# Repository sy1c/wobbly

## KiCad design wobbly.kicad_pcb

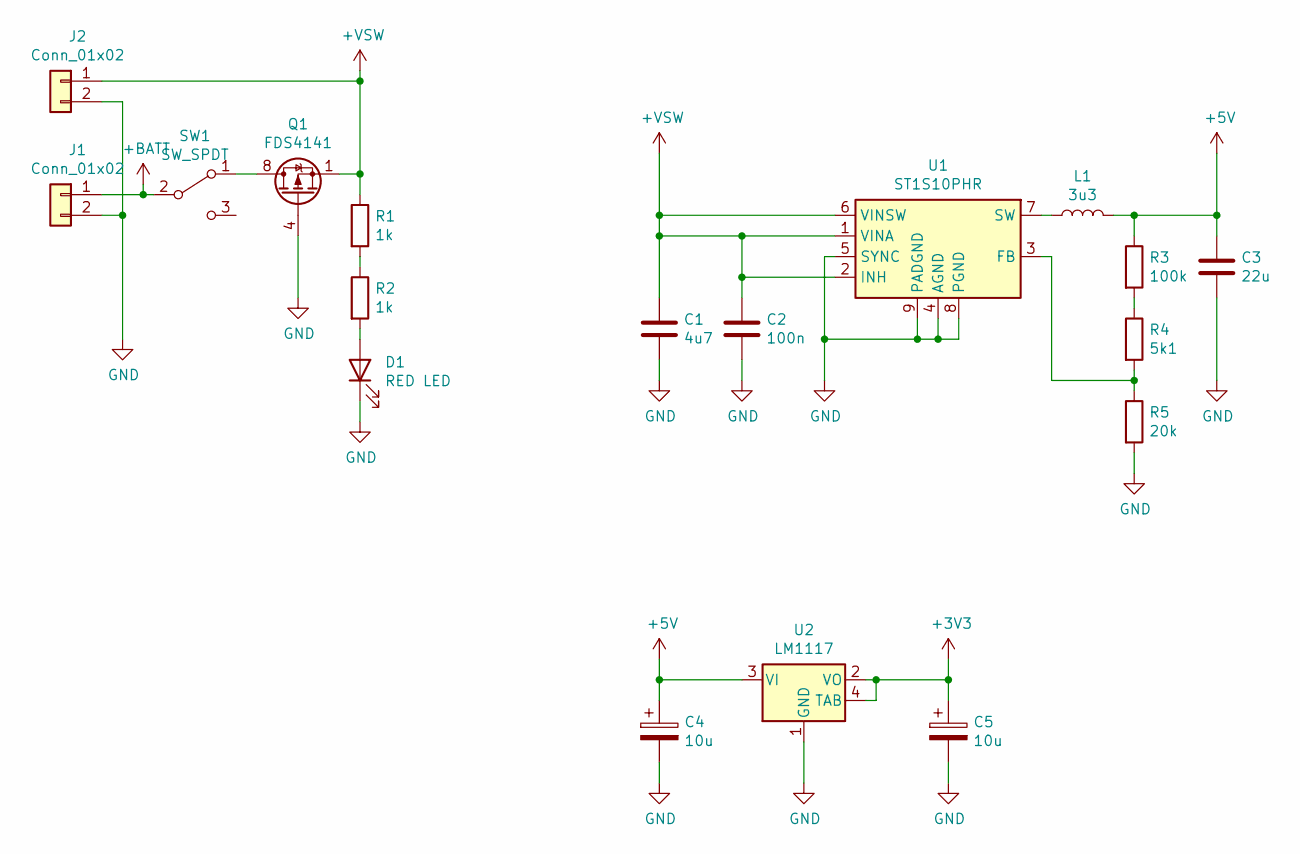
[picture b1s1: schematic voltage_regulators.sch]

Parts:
C1: 4u7; C_1206
C2: 100n; C_1206
C3: 22u; C_1210_Pad1.40x2.80mm
C4, C5: 10u; CP_2312
D1: RED LED; LED_0805
J1, J2: Conn_01x02; Degson_15EDGRC-3.5
L1: 3u3; L_TDK_RLF7030
Q1: FDS4141; SO-8
R1, R2: 1k; R_1206
R3: 100k; R_1206
R4: 5k1; R_1206
R5: 20k; R_1206
SW1: SW_SPDT; SW_Slide_CE_SL19121
U1: ST1S10PHR; Power_SO-8
U2: LM1117; SOT-223-4

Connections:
+3V3: C5.1, U2.2 (VO), U2.4 (TAB); also elsewhere on the board
+5V: C3.1, C4.1, L1.2, R3.1, U2.3 (VI); also elsewhere on the board
+BATT: J1.1, SW1.2 (B)
GND: C1.2, C2.2, C3.2, C4.2, C5.2, D1.1 (K), J1.2, J2.2, Q1.4 (G), R5.2, U1.4 (AGND), U1.5 (SYNC), U1.8 (PGND), U1.9 (PADGND), U2.1 (GND); also elsewhere on the board
unnamed: D1.2 (A), R2.2
unnamed: L1.1, U1.7 (SW)
unnamed: Q1.5 (D), Q1.6 (D), Q1.7 (D), Q1.8 (D), SW1.1 (A)
unnamed: R1.2, R2.1
unnamed: R3.2, R4.1
unnamed: R4.2, R5.1, U1.3 (FB)

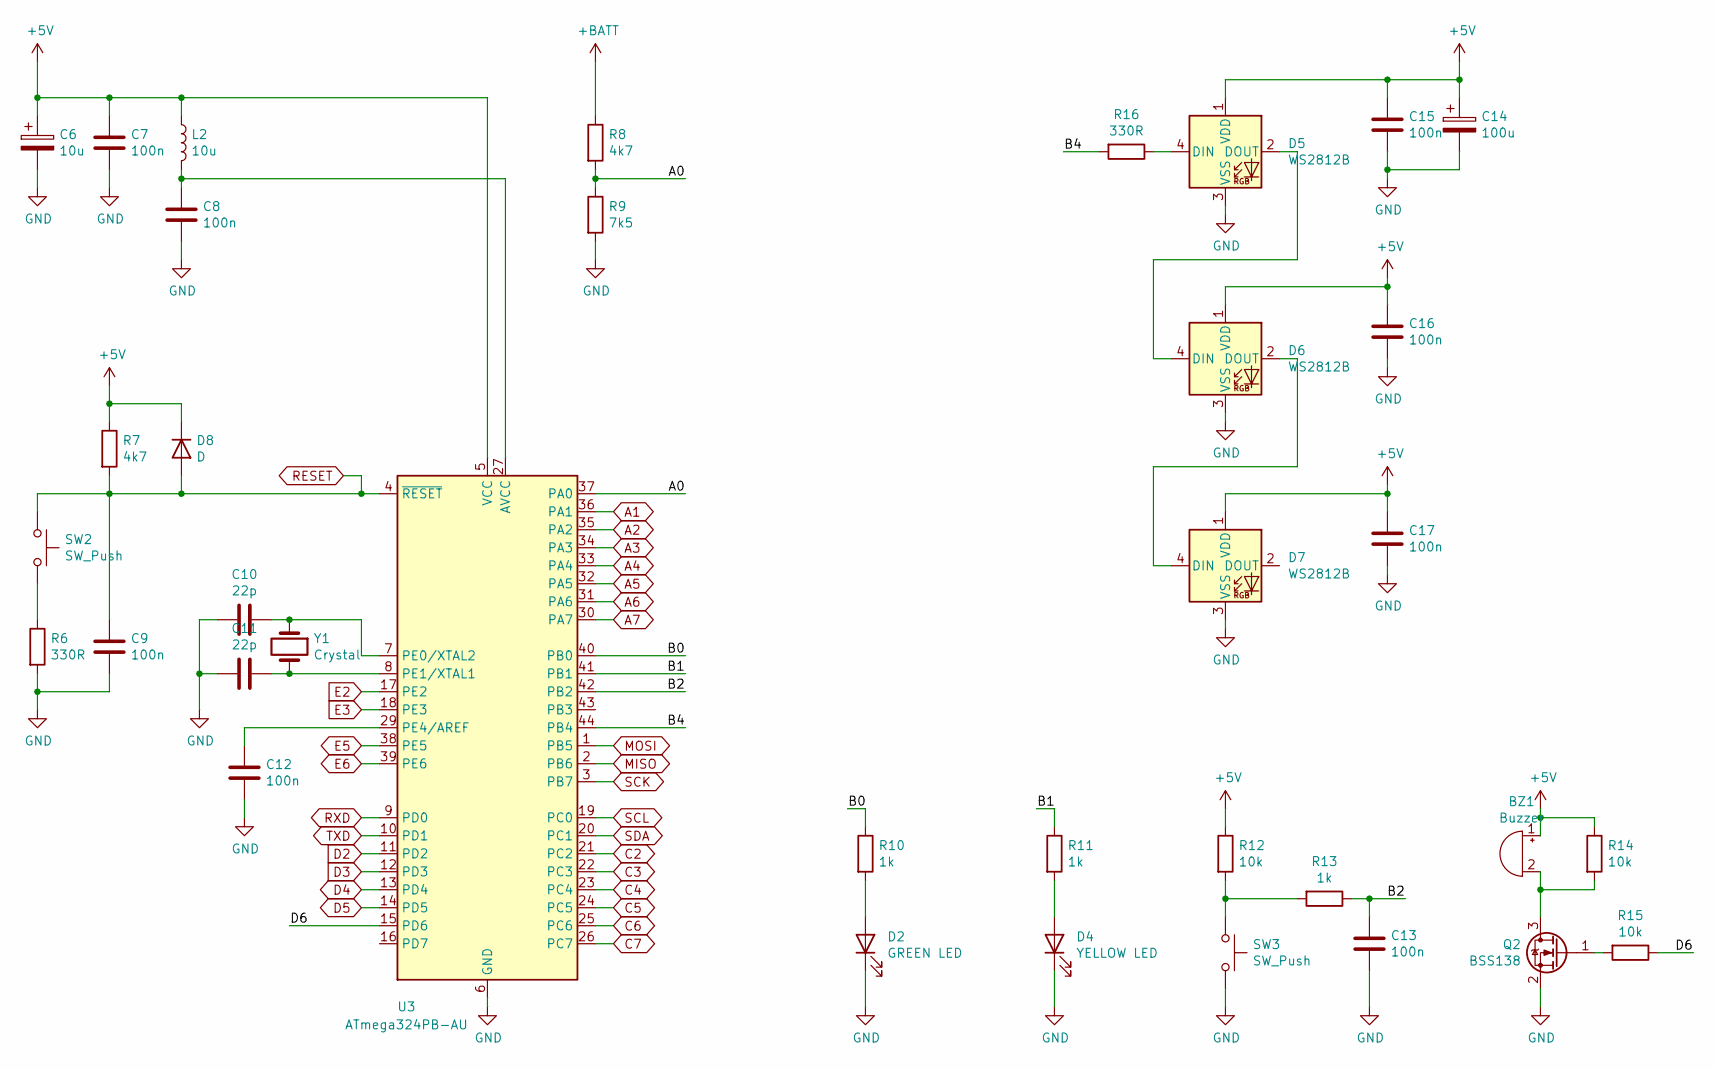
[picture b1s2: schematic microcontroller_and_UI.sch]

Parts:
BZ1: Buzzer; Buzzer_13.8x6.8RM7.6
C6: 10u; CP_2312
C7, C8, C9, C12, C13, C15, C16, C17: 100n; C_1206
C10, C11: 22p; C_1206
C14: 100u; CP_Elec_6.3x5.8
D2: GREEN LED; LED_0805
D4: YELLOW LED; LED_0805
D5, D6, D7: WS2812B; LED_WS2812B
D8: D; D_SOD-80
L2: 10u; L_TDK_NLC453232
Q2: BSS138; SOT-23
R6, R16: 330R; R_1206
R7, R8: 4k7; R_1206
R9: 7k5; R_1206
R10, R11, R13: 1k; R_1206
R12, R14, R15: 10k; R_1206
SW2, SW3: SW_Push; SW_Push_CK_KMR2
U3: ATmega324PB-AU; TQFP-44
Y1: Crystal; Crystal_HC49US

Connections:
+5V: BZ1.1 (-), C6.1, C7.1, C14.1, C15.1, C16.1, C17.1, D5.1 (VDD), D6.1 (VDD), D7.1 (VDD), D8.1 (K), L2.1, R7.1, R12.1, R14.1, U3.5 (VCC); also elsewhere on the board
/Microcontroller and UI/A0: R8.2, R9.1, U3.37 (PA0)
/Microcontroller and UI/B0: R10.1, U3.40 (PB0)
/Microcontroller and UI/B1: R11.1, U3.41 (PB1)
/Microcontroller and UI/B2: C13.1, R13.1, U3.42 (PB2)
/Microcontroller and UI/B4: R16.2, U3.44 (PB4)
/Microcontroller and UI/D6: R15.1, U3.15 (PD6)
A1: U3.36 (PA1); also elsewhere on the board
A2: U3.35 (PA2); also elsewhere on the board
A3: U3.34 (PA3); also elsewhere on the board
A4: U3.33 (PA4); also elsewhere on the board
A5: U3.32 (PA5); also elsewhere on the board
A6: U3.31 (PA6); also elsewhere on the board
A7: U3.30 (PA7); also elsewhere on the board
C2: U3.21 (PC2); also elsewhere on the board
C3: U3.22 (PC3); also elsewhere on the board
C4: U3.23 (PC4); also elsewhere on the board
C5: U3.24 (PC5); also elsewhere on the board
C6: U3.25 (PC6); also elsewhere on the board
C7: U3.26 (PC7); also elsewhere on the board
D2: U3.11 (PD2); also elsewhere on the board
D3: U3.12 (PD3); also elsewhere on the board
D4: U3.13 (PD4); also elsewhere on the board
D5: U3.14 (PD5); also elsewhere on the board
E2: U3.17 (PE2); also elsewhere on the board
E3: U3.18 (PE3); also elsewhere on the board
E5: U3.38 (PE5); also elsewhere on the board
E6: U3.39 (PE6); also elsewhere on the board
GND: C6.2, C7.2, C8.2, C9.2, C10.2, C11.2, C12.2, C13.2, C14.2, C15.2, C16.2, C17.2, D2.1 (K), D4.1 (K), D5.3 (VSS), D6.3 (VSS), D7.3 (VSS), Q2.2 (S), R6.2, R9.2, SW3.2, U3.6 (GND), U3.28 (GND); also elsewhere on the board
MISO: U3.2 (PB6); also elsewhere on the board
MOSI: U3.1 (PB5); also elsewhere on the board
unnamed: BZ1.2 (+), Q2.3 (D), R14.2
unnamed: C8.1, L2.2, U3.27 (AVCC)
unnamed: C10.1, U3.7 (PE0/XTAL2), Y1.1
unnamed: C11.1, U3.8 (PE1/XTAL1), Y1.2
unnamed: C12.1, U3.29 (PE4/AREF)
unnamed: D2.2 (A), R10.2
unnamed: D4.2 (A), R11.2
unnamed: D5.2 (DOUT), D6.4 (DIN)
unnamed: D5.4 (DIN), R16.1
unnamed: D6.2 (DOUT), D7.4 (DIN)
unnamed: Q2.1 (G), R15.2
unnamed: R6.1, SW2.2
unnamed: R12.2, R13.2, SW3.1
RESET: C9.1, D8.2 (A), R7.2, SW2.1, U3.4 (~RESET); also elsewhere on the board
RXD: U3.9 (PD0); also elsewhere on the board
SCK: U3.3 (PB7); also elsewhere on the board
SCL: U3.19 (PC0); also elsewhere on the board
SDA: U3.20 (PC1); also elsewhere on the board
TXD: U3.10 (PD1); also elsewhere on the board

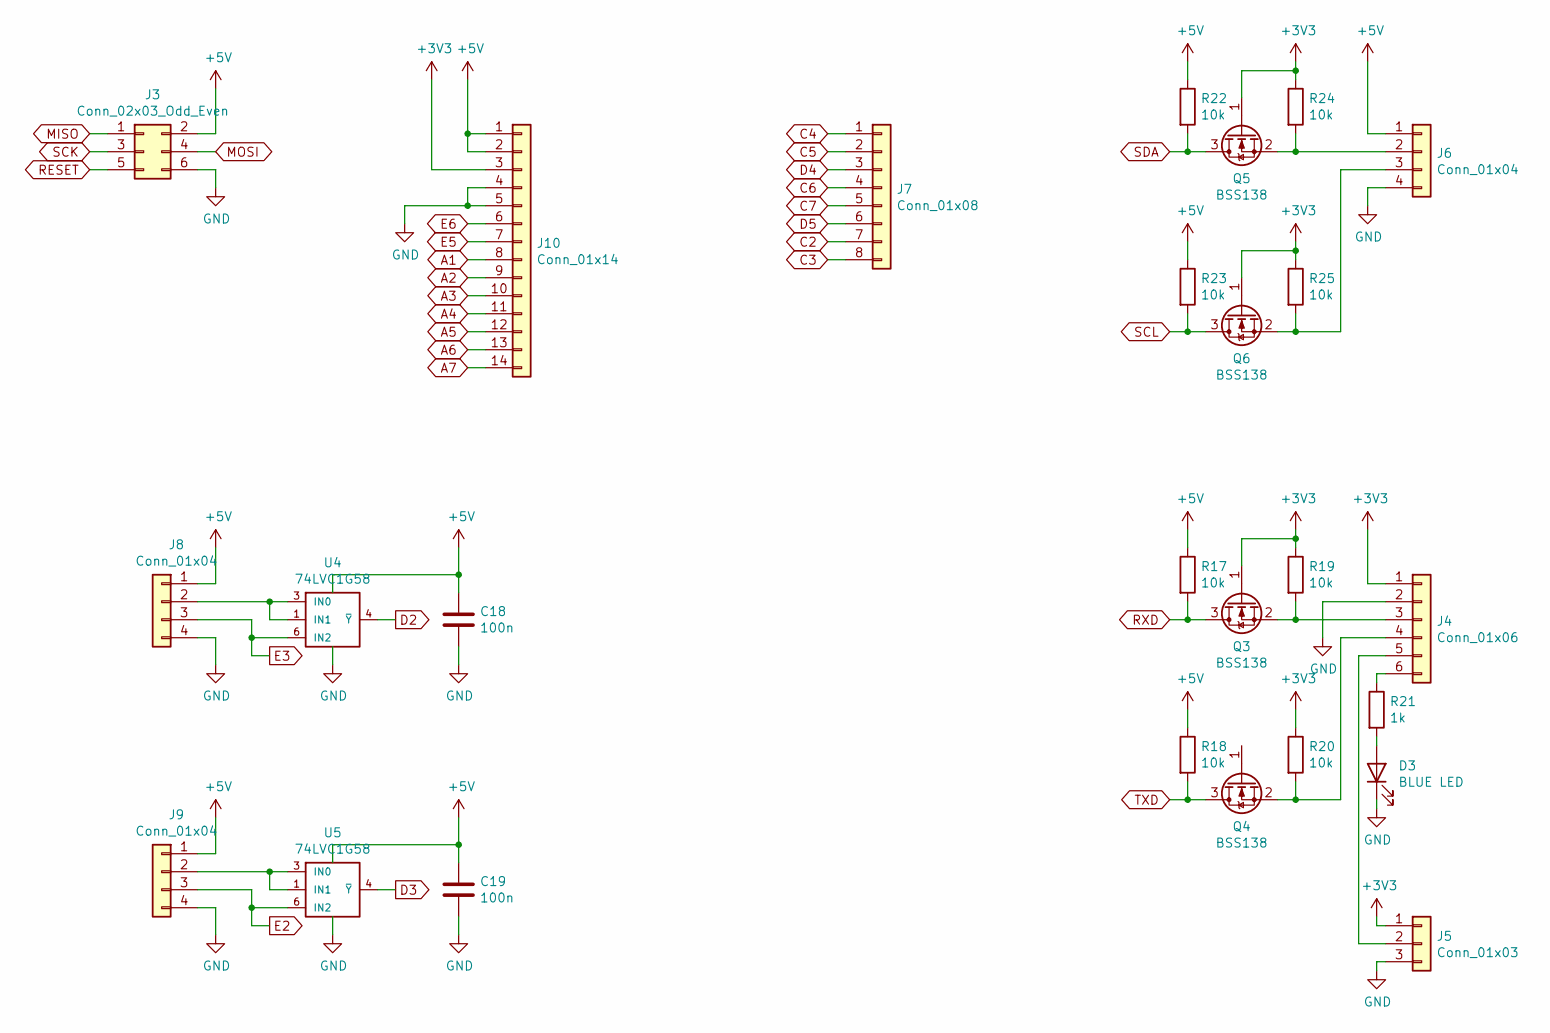
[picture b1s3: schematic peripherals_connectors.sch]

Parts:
C18, C19: 100n
D3: BLUE LED
J3: Conn_02x03_Odd_Even
J4: Conn_01x06
J5: Conn_01x03
J6, J8, J9: Conn_01x04
J7: Conn_01x08
J10: Conn_01x14
Q3, Q4, Q5, Q6: BSS138; SOT-23
R17, R18, R19, R20, R22, R23, R24, R25: 10k
R21: 1k
U4, U5: 74LVC1G58

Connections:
+3V3: J4.1, J5.1, J10.3, Q3.1 (G), Q4.1 (G), Q5.1 (G), Q6.1 (G), R19.1, R20.1, R24.1, R25.1; also elsewhere on the board
+5V: C18.1, C19.1, J3.2, J6.1, J8.1, J9.1, J10.1, J10.2, R17.1, R18.1, R22.1, R23.1, U4.5 (VCC), U5.5 (VCC); also elsewhere on the board
A1: J10.8; also elsewhere on the board
A2: J10.9; also elsewhere on the board
A3: J10.10; also elsewhere on the board
A4: J10.11; also elsewhere on the board
A5: J10.12; also elsewhere on the board
A6: J10.13; also elsewhere on the board
A7: J10.14; also elsewhere on the board
C2: J7.7; also elsewhere on the board
C3: J7.8; also elsewhere on the board
C4: J7.1; also elsewhere on the board
C5: J7.2; also elsewhere on the board
C6: J7.4; also elsewhere on the board
C7: J7.5; also elsewhere on the board
D2: U4.4 (~Y); also elsewhere on the board
D3: U5.4 (~Y); also elsewhere on the board
D4: J7.3; also elsewhere on the board
D5: J7.6; also elsewhere on the board
E2: J9.3, U5.6 (IN2); also elsewhere on the board
E3: J8.3, U4.6 (IN2); also elsewhere on the board
E5: J10.7; also elsewhere on the board
E6: J10.6; also elsewhere on the board
GND: C18.2, C19.2, D3.1 (K), J3.6, J4.2, J5.3, J6.4, J8.4, J9.4, J10.4, J10.5, U4.2 (GND), U5.2 (GND); also elsewhere on the board
MISO: J3.1; also elsewhere on the board
MOSI: J3.4; also elsewhere on the board
unnamed: D3.2 (A), R21.2
unnamed: J4.3, Q3.2 (S), R19.2
unnamed: J4.4, Q4.2 (S), R20.2
unnamed: J4.5, J5.2
unnamed: J4.6, R21.1
unnamed: J6.2, Q5.2 (S), R24.2
unnamed: J6.3, Q6.2 (S), R25.2
unnamed: J8.2, U4.1 (IN1), U4.3 (IN0)
unnamed: J9.2, U5.1 (IN1), U5.3 (IN0)
RESET: J3.5; also elsewhere on the board
RXD: Q3.3 (D), R17.2; also elsewhere on the board
SCK: J3.3; also elsewhere on the board
SCL: Q6.3 (D), R23.2; also elsewhere on the board
SDA: Q5.3 (D), R22.2; also elsewhere on the board
TXD: Q4.3 (D), R18.2; also elsewhere on the board

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
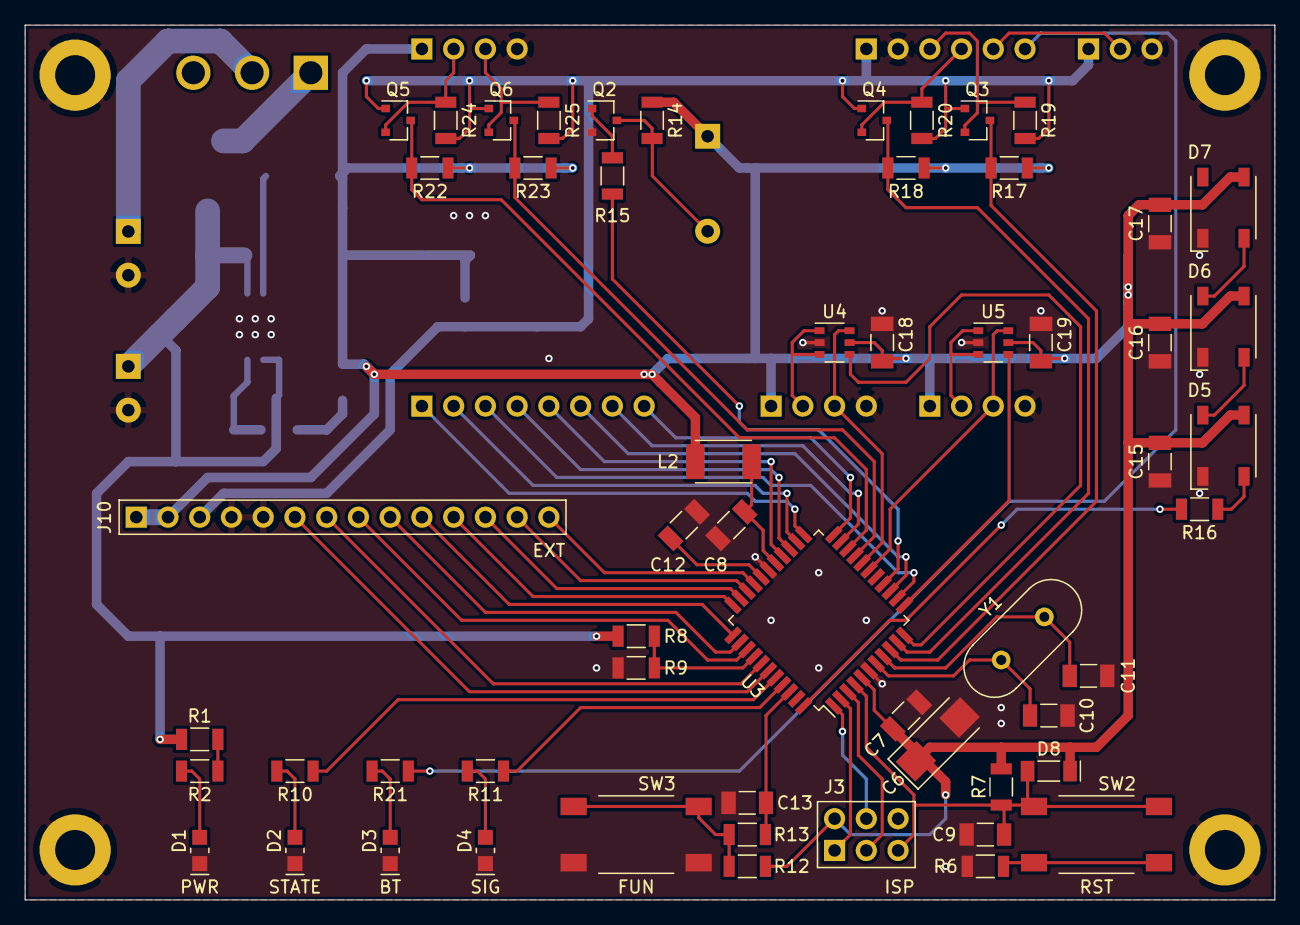
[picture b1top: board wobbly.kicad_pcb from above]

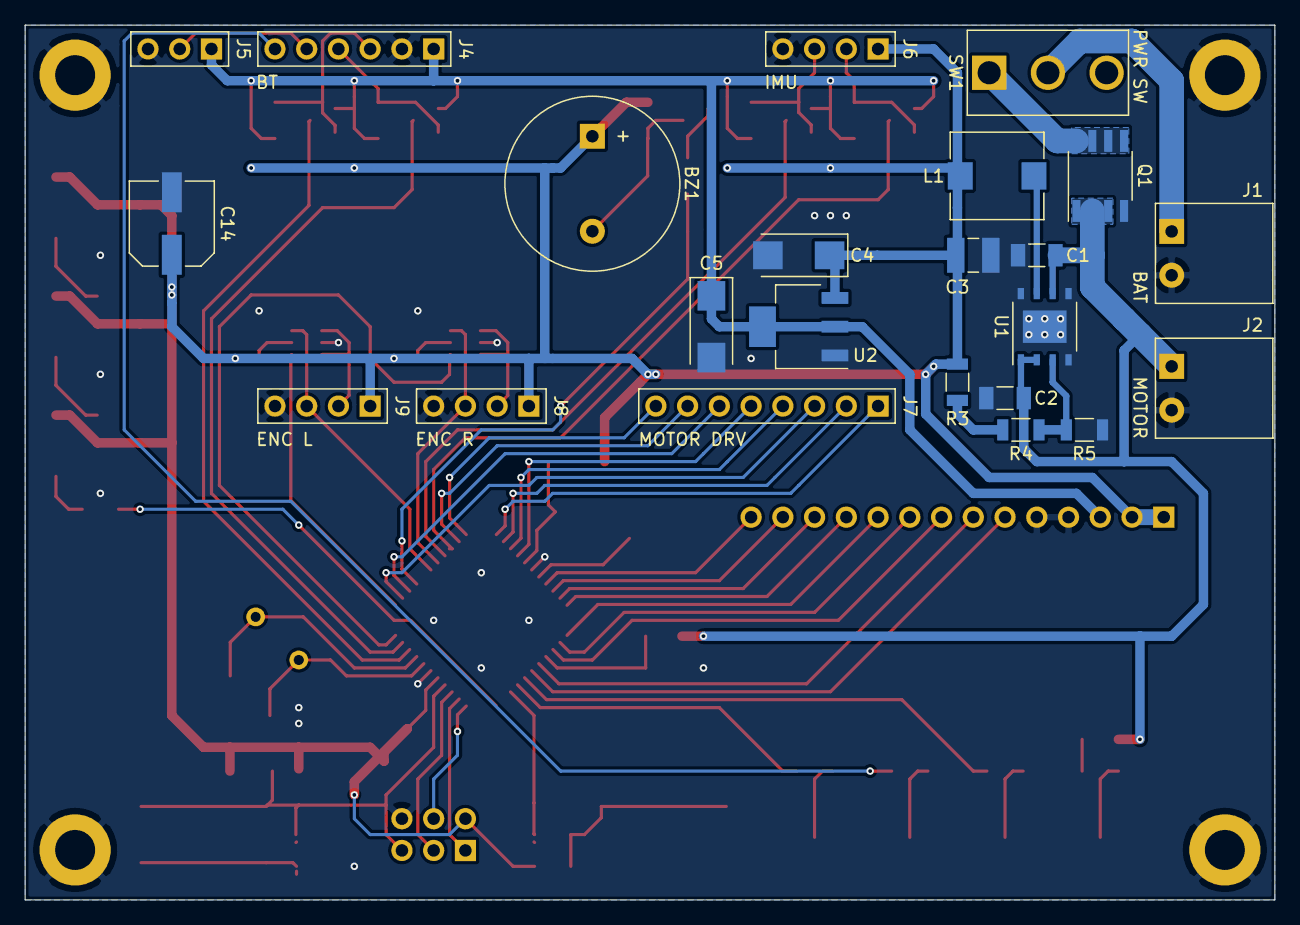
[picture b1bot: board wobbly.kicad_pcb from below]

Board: 2 copper layers, 100.0 x 70.0 mm, 84 parts (23 on the bottom side), 68 nets.

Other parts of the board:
H1, H2, H3, H4: MountingHole_Pad; MountingHole_3.2mm_M3_ISO7380_Pad

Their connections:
GND: H1.1, H2.1, H3.1, H4.1; also elsewhere on the board

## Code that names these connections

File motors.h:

#define MOTL_R PC4
#define MOTL_F PC5
#define MOTL_PWM PD4
#define MOTR_F PC6
#define MOTR_R PC7
#define MOTR_PWM PD5

void motors_init(void);
void motors_left_speed(uint8_t speed);
void motors_right_speed(uint8_t speed);
void motors_set_speed(uint8_t left_speed, uint8_t right_speed);

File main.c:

/*
 * File:   main.c
 * Author: Mateusz Szymiec
 *
 * Created on July 24, 2021, 1:23 AM
 */

#define F_CPU 16000000UL
#define BAUD 9600

#define BATT PA0
#define STATE_LED PB0
#define SIG_LED PB1
#define FUN_BTN PB2
#define BUZZER PD6

#include <avr/io.h>
#include <avr/interrupt.h>
#include <util/delay.h>

#include "imu.h"
#include "twi.h"
#include "adc.h"
#include "timer.h"
#include "usart.h"
#include "motors.h"
#include "encoders.h"

/*
FUSES = {
	.low = 0xFF, // LOW {SUT_CKSEL=EXTXOSC_8MHZ_XX_16KCK_14CK_65MS, CKOUT=CLEAR, CKDIV8=CLEAR}
	.high = 0xD9, // HIGH {BOOTRST=CLEAR, BOOTSZ=2048W_3800, EESAVE=CLEAR, WDTON=CLEAR, SPIEN=SET, JTAGEN=CLEAR, OCDEN=CLEAR}
	.extended = 0xF7, // EXTENDED {BODLEVEL=DISABLED, CFD=CFD_DISABLED}
};

LOCKBITS = 0xFF; // {LB=NO_LOCK, BLB0=NO_LOCK, BLB1=NO_LOCK}
*/

uint16_t left_speed, right_speed;

void state(uint8_t batt);

int main(void) {
    
    DDRA &= ~(1 << BATT);
    DDRB |= (1 << STATE_LED) | (1 << SIG_LED);
    DDRB &= ~(1 << FUN_BTN);
    
    timer1_init();
    timer3_init();
    usart_init();
    twi_init();
    adc_init();
    motors_init();
    encoders_init();
    
    imu_init();
    
    imu_calibrate();
   
    _delay_ms(1000);
    
    sei();
    
    while (1) {
        state(ADCH);
        
        if (PINB & (1 << FUN_BTN)) {
            PORTC &= ~(1 << MOTL_F);
            PORTC &= ~(1 << MOTL_R);
            PORTC &= ~(1 << MOTR_F);
            PORTC &= ~(1 << MOTR_R);
        }
        else {
            motors_set_speed(128, 128);
            PORTC |= (1 << MOTL_F) | (1 << MOTR_F);
        }
        
        usart_transmit(right_speed);
    }
    
    return(0);
}


void state(uint8_t batt) {
    if (batt > 198) {
        PORTB |= (1 << STATE_LED);
    }
    else {
        PORTB &= ~(1 << STATE_LED);
    }
}

//ISR(TIMER0_OVF_vect) {    
//    
//}

ISR(TIMER3_COMPA_vect) {
    imu_read();
    imu_integrate_gyro();
    
    right_speed = encoders_right_counts();
}

ISR(USART0_RX_vect) {
    uint8_t command;
    command = usart_receive();
    
    if (command == 0x00) {
        PORTB ^= (1 << SIG_LED);
    }
}

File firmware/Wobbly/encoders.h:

#define ENCL_XOR PD3
#define ENCL_B PE2
#define ENCR_XOR PD2
#define ENCR_B PE3

volatile uint8_t left_A, left_B, right_A, right_B;
volatile uint16_t left_count, right_count;

void encoders_init(void);
int16_t encoders_left_counts(void);
int16_t encoders_right_counts(void);

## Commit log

2021-02-09 Add 3D design project files
2021-02-10 Add mounting plate to 3d design
2021-02-11 Add motors brackets to design
2021-02-11 Add motors to design
2021-02-13 Add wheels to design
2021-02-13 Add cover plate to design
2021-02-15 Add battery to design
2021-02-15 Add main PCB to design
2021-03-22 Change PCB size in design
2021-05-29 Add voltage regulators schematic
2021-05-29 Add uC circuit and UI schematic
2021-05-30 Add connectors schematic
2021-05-30 Annotate schematic symbols
2021-06-27 Assign PCB footprints
2021-07-11 Change width of the plates
2021-07-11 Add PCB layout
2021-07-15 Rename file
2021-07-15 Update and rename files
2021-07-15 Add graphics
2021-07-15 Generate gerbers files
2021-07-23 Add project files
2021-07-24 Add .gitignore file
2021-07-24 Update project files
2021-08-07 Add bluetooth communication functions
2021-08-08 Add battery voltage measurement
2021-08-08 Change R8 and R9 values
2021-09-13 Refactor and add IMU reading
2021-09-25 Add motors control
2021-09-27 Measure the rotational speed of the wheels
2023-07-19 Move project files to 3d-model/Wobbly
2023-07-19 Move project files to pcb/Wobbly
2023-07-19 Move project files to firmware/Wobbly
